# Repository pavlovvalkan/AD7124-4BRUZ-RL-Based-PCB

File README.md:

AD7124-4BRUZ-RL Based PCB for Two 4-Wire P100 RTD Kelvin Measurement
Project Description

This project involves a printed circuit board (PCB) designed in KiCad and utilizes the AD7124-4BRUZ-RL analog-to-digital converter (ADC).
The PCB is specifically tailored for high-precision temperature measurements using the 4-Wire Kelvin method with P100 Resistance Temperature Detector (RTD) sensors.
Key Features

    ADC: AD7124-4BRUZ-RL, a 24-bit, low-noise, precision ADC with configurable inputs and low power consumption.
    Temperature Measurement: Supports 4-Wire connection for accurate Kelvin measurement of P100 RTD sensors.

Purpose

The project aims to provide a robust platform for precise temperature sensing applications, leveraging the capabilities of the AD7124-4BRUZ-RL ADC and ensuring accurate measurement
through the use of 4-Wire Kelvin connections.

This description highlights the focus on temperature measurement accuracy and the integration of specific components within the KiCad environment.

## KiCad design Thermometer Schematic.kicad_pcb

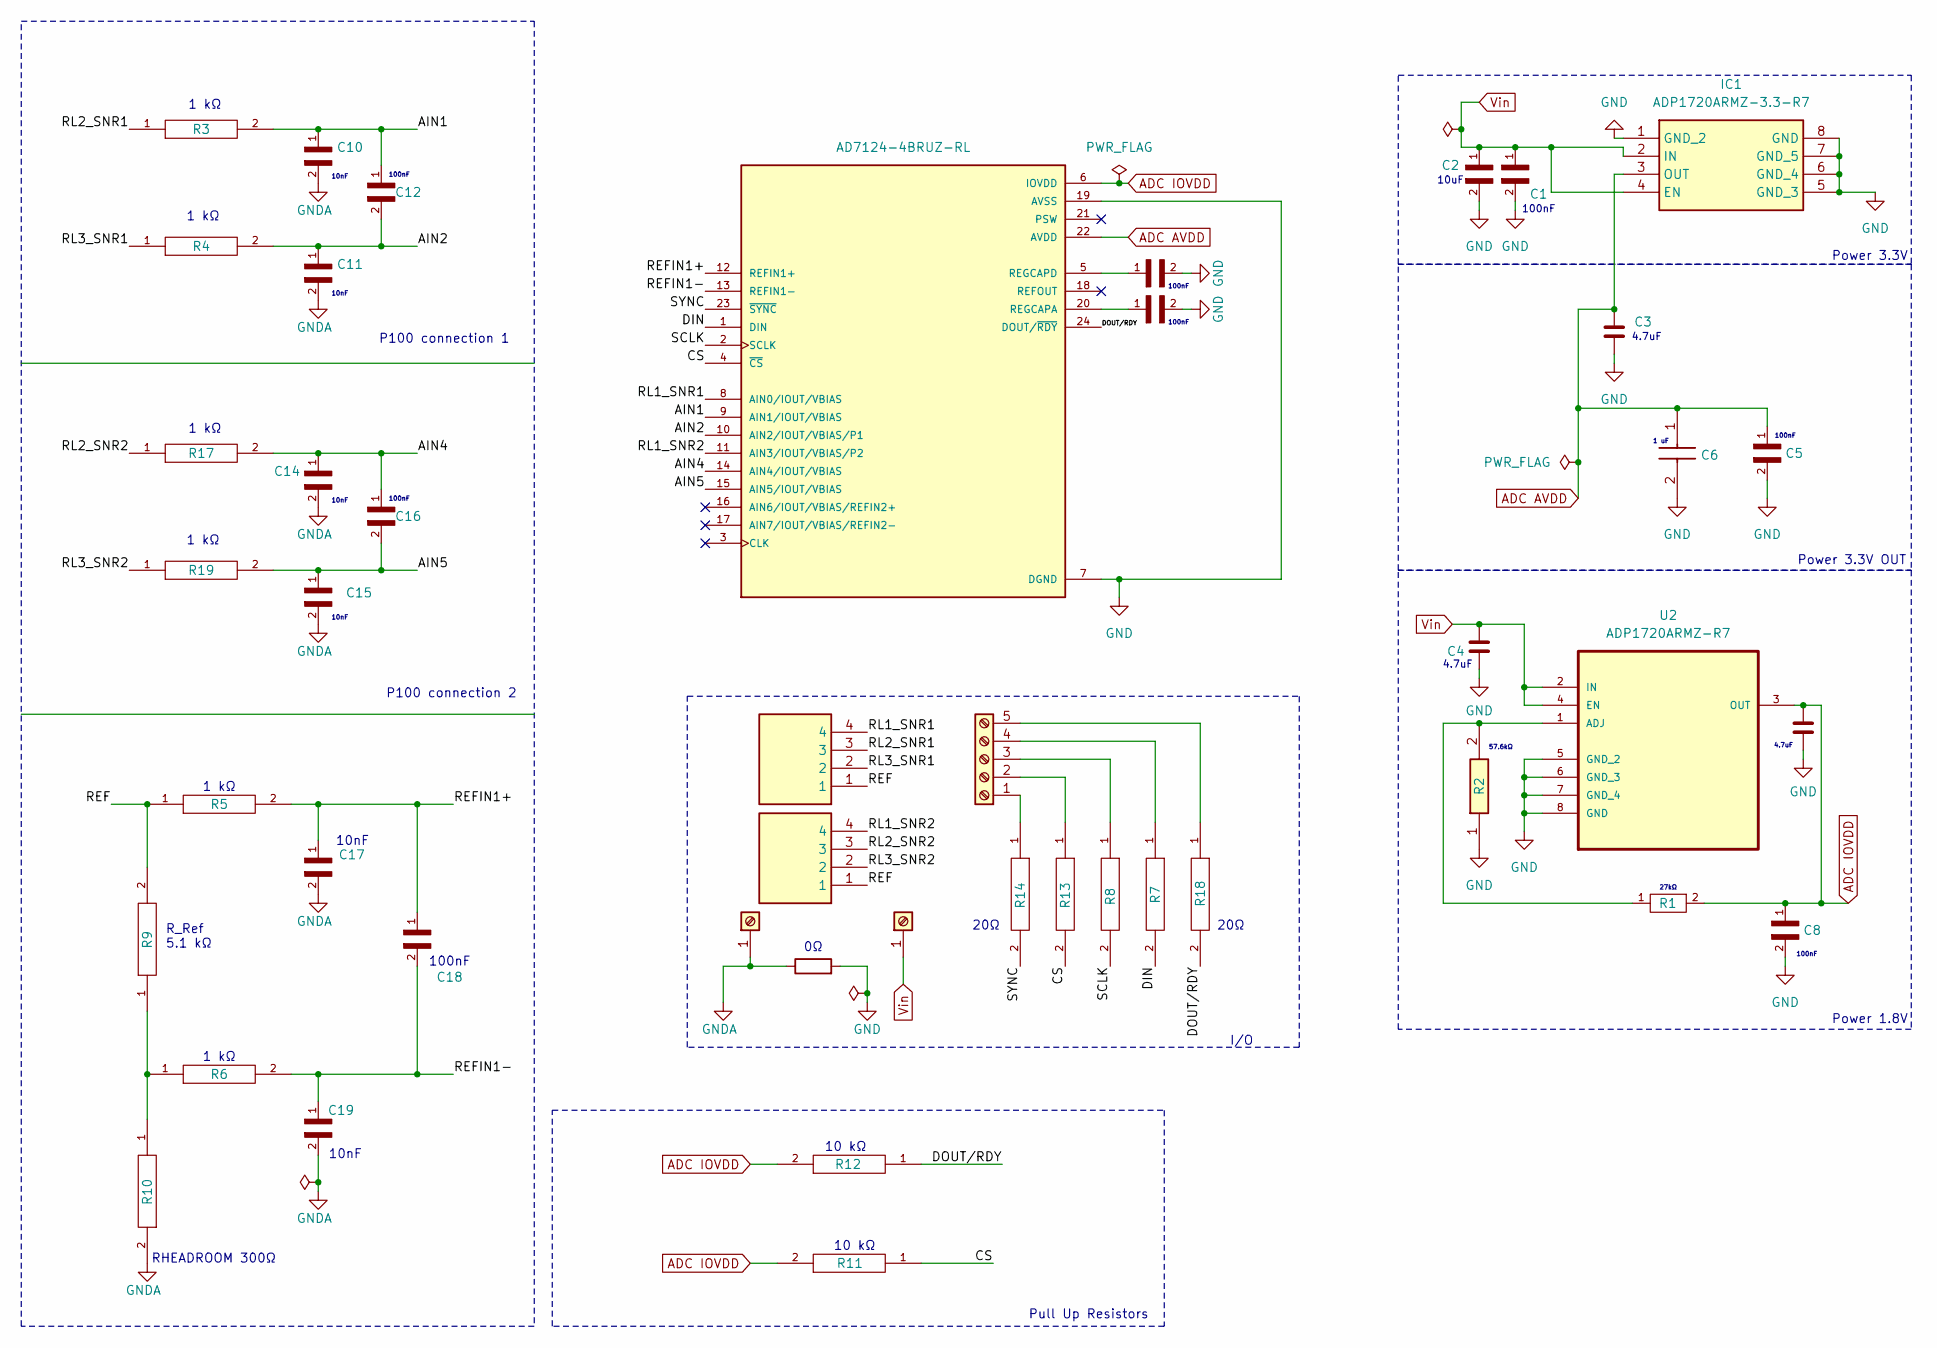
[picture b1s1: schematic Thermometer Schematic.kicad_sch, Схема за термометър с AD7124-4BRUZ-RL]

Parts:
C1, C5, C8, C9, C12, C13, C16, C18: 08055C104J4Z2A; CAPC2012X94N
C2: CGA5L3X5R1H106K160AB; CAPC3216X190N
C3, C4, C7: CC0805ZKY5V7BB475; PartN CC0805ZKY5V7BB475
C6: C1206F105M5RACAUTO7210; C1206; Mouser Part Number 80-C1206F105M5RAUTLR
C10, C11, C14, C15, C17, C19: GCM155R71H103KA55D; CAPC1005X55N
IC1: ADP1720ARMZ-3.3-R7; SOP65P490X110-8N; Manufacturer_Part_Number ADP1720ARMZ-3.3-R7; Mouser Part Number 584-ADP1720ARMZ3.3R7
J2: Screw_Terminal_01x05; PinHeader_1x05_P2.54mm_Vertical
J3, J4: CTB5202_4; CTB52024; Manufacturer_Part_Number CTB5202/4
J5: VIn; PinHeader_1x01_P2.54mm_Vertical
J6: GND; PinHeader_1x01_P2.54mm_Vertical
R1: ERJ-3GEYJ273V; RESC1608X55
R2: CRCW060357K6FKEA; RESC1608X50N; Manufacturer_Part_Number CRCW060357K6FKEA
R3, R4, R5, R6, R17, R19: CRCW08051K00JNEA; RESC2012X50N
R7, R8, R13, R14, R18: ERJ-UP6D20R0V; RES_ERJ-UP6D20R0V; PARTREV 3/1/2020
R9: ERA6AEB512V; RES_ERA6AEB512V; PARTREV 3/1/2020
R10: ERA2AEB301X; RES_ERA2AEB301X; PARTREV 3/1/2020
R11, R12: RT0402FRE0710KL; RESC1005X35N
R15: R; CAPC1005X55N
U1: AD7124-4BRUZ-RL; SOP65P640X120-24N; PARTREV D
U2: ADP1720ARMZ-R7; SOP65P490X110-8N; MPN ADP1720ARMZ-R7

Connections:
/AIN1: C10.1, C12.1, R3.2, U1.9 (AIN1/IOUT/VBIAS)
/AIN2: C11.1, C12.2, R4.2, U1.10 (AIN2/IOUT/VBIAS/P1)
/AIN4: C14.1, C16.1, R17.2, U1.14 (AIN4/IOUT/VBIAS)
/AIN5: C15.1, C16.2, R19.2, U1.15 (AIN5/IOUT/VBIAS)
/CS: R11.1, R13.2, U1.4 (~CS)
/DIN: R7.2, U1.1 (DIN)
/DOUT/RDY: R12.1, R18.2, U1.24 (DOUT/~RDY)
/REF: J3.1, J4.1, R5.1, R9.2
/REFIN1+: C17.1, C18.1, R5.2, U1.12 (REFIN1+)
/REFIN1-: C18.2, C19.1, R6.2, U1.13 (REFIN1-)
/RL1_SNR1: J3.4, U1.8 (AIN0/IOUT/VBIAS)
/RL1_SNR2: J4.4, U1.11 (AIN3/IOUT/VBIAS/P2)
/RL2_SNR1: J3.3, R3.1
/RL2_SNR2: J4.3, R17.1
/RL3_SNR1: J3.2, R4.1
/RL3_SNR2: J4.2, R19.1
/SCLK: R8.2, U1.2 (SCLK)
/SYNC: R14.2, U1.23 (~SYNC)
ADC AVDD: C3.2, C5.1, C6.1, IC1.3 (OUT), U1.22 (AVDD)
ADC IOVDD: C7.2, C8.1, R1.2, R11.2, R12.2, U1.6 (IOVDD), U2.3 (OUT)
GND: C1.2, C2.2, C3.1, C4.1, C5.2, C6.2, C7.1, C8.2, C9.2, C13.2, IC1.1 (GND_2), IC1.5 (GND_3), IC1.6 (GND_4), IC1.7 (GND_5), IC1.8 (GND), R2.1, R15.2, U1.7 (DGND), U1.19 (AVSS), U2.5 (GND_2), U2.6 (GND_3), U2.7 (GND_4), U2.8 (GND)
GNDA: C10.2, C11.2, C14.2, C15.2, C17.2, C19.2, J6.1, R10.2, R15.1
unnamed: J2.1, R14.1
unnamed: J2.2, R13.1
unnamed: J2.3, R8.1
unnamed: J2.4, R7.1
unnamed: J2.5, R18.1
unnamed: R6.1, R9.1, R10.1
unnamed: C9.1, U1.20 (REGCAPA)
unnamed: C13.1, U1.5 (REGCAPD)
unnamed: R1.1, R2.2, U2.1 (ADJ)
Vin: C1.1, C2.1, C4.2, IC1.2 (IN), IC1.4 (EN), J5.1, U2.2 (IN), U2.4 (EN)

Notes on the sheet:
10nF
1 uF
1 kΩ
4.7uF
20Ω
Power 3.3V
R_Ref 5.1 kΩ
P100 connection 1
RHEADROOM 300Ω
Power 3.3V OUT
100nF
10 kΩ
Power 1.8V
I/O
10uF
27kΩ
P100 connection 2
Pull Up Resistors
57.6kΩ

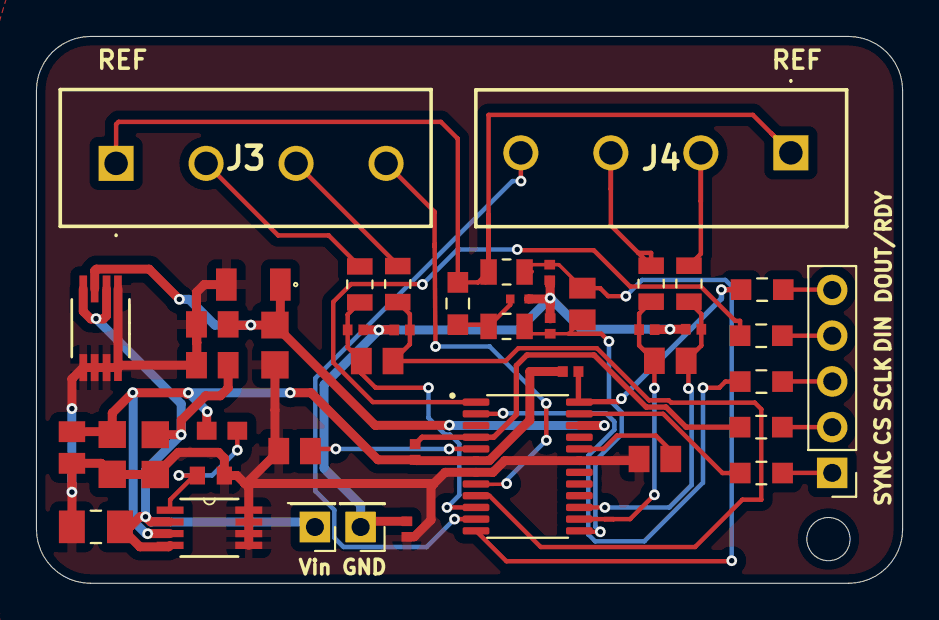
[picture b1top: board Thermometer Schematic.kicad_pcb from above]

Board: 2 copper layers, 48.1 x 30.4 mm, 45 parts (0 on the bottom side), 32 nets.

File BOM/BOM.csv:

"Reference","Value","Datasheet","Footprint","Qty","DNP"
"C1,C5,C8,C9,C12,C13,C16,C18","08055C104J4Z2A","","08055C104J4Z2A:CAPC2012X94N","8",""
"C2","CGA5L3X5R1H106K160AB","","CGA5L3X5R1H106K160AB:CAPC3216X190N","1",""
"C3,C4,C7","CC0805ZKY5V7BB475","","CC0805ZKY5V7BB475:CC0805ZKY5V7BB475","3",""
"C6","C1206F105M5RACAUTO7210","https://content.kemet.com/datasheets/KEM_C1012_X7R_OPENMODE_SMD.pdf","C1206F105M5RACAUTO7210:C1206","1",""
"C10,C11,C14,C15,C17,C19","GCM155R71H103KA55D","","GCM155R71H103KA55D:CAPC1005X55N","6",""
"IC1","ADP1720ARMZ-3.3-R7","http://componentsearchengine.com/Datasheets/1/ADP1720ARMZ-3.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","ADP1720ARMZ-3.3-R7:SOP65P490X110-8N","1",""
"J2","Screw_Terminal_01x05","~","Connector_PinHeader_2.54mm:PinHeader_1x05_P2.54mm_Vertical","1",""
"J3,J4","CTB5202_4","https://www.camdenboss.com/products/datasheet/CTB5202%20seri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","CTB5202_4:CTB52024","2",""
"J5","VIn","~","Connector_PinHeader_2.54mm:PinHeader_1x01_P2.54mm_Vertical","1",""
"J6","GND","~","Connector_PinHeader_2.54mm:PinHeader_1x01_P2.54mm_Vertical","1",""
"R1","ERJ-3GEYJ273V","","ERJ3GEYJ273V:RESC1608X55","1",""
"R2","CRCW060357K6FKEA","http://www.vishay.com/docs/20035/dcrcwe3.pdf","CRCW060357K6FKEA:RESC1608X50N","1",""
"R3,R4,R5,R6,R17,R19","CRCW08051K00JNEA ","","CRCW08051K00JNEA:RESC2012X50N","6",""
"R7,R8,R13,R14,R18","ERJ-UP6D20R0V","","ERJ-UP6D20R0V:RES_ERJ-UP6D20R0V","5",""
"R9","ERA6AEB512V","","ERA6AEB512V:RES_ERA6AEB512V","1",""
"R10","ERA2AEB301X","","ERA2AEB301X:RES_ERA2AEB301X","1",""
"R11,R12","RT0402FRE0710KL","","RT0402FRE0710KL:RESC1005X35N","2",""
"R15","R","~","GCM155R71H103KA55D:CAPC1005X55N","1",""
"U1","AD7124-4BRUZ-RL","","AD7124-4BRUZ-RL:SOP65P640X120-24N","1",""
"U2","ADP1720ARMZ-R7","","ADP1720ARMZ-R7:SOP65P490X110-8N","1",""
